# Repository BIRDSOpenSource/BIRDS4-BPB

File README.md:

<div align="center">
  
</div>

# BIRDS4-BPB
 Documentation for the Backplane Board used in the BIRDS4 Satellite

## About the BIRDS4 Program:

The Mission Statement of the Project is:

> “By successfully building and operating first satellite of nation, advance toward indigenous space program in each country”

The project is led by Kyushu Institute of Technology in Japan and involves students from Philippines, Paraguay, Nepal, Turkey and Japan.

Satellite Names: Tsuru (Japan), Guarani-1 (Paraguay) and Maya-2 (Phillipines)

Stakeholders:  Paraguayan Space Agency, Polytechnic Faculty of National University of Asuncion, and Kyushu Institute of Technology (Kyutech) for Japan.

Project duration: 2018-2022

CubeSat: 1U (10x10x10) cm3

Weight: 1.13kg

Launch Date: 21st February 2021 

BIRDS-4 has 1 main missions in total; APRS Store and forward mission

## Organisation structure

```bash

├── .gitattributes
├── B4_BPB_FM_PartsList_PBan_20191024.xls
├── BPB_v16.brd
├── BPB_v16.pdf
├── BPB_v16.sch
├── BPB_v16_BOT.png
├── BPB_v16_TOP.png
├── LICENSE
├── Photo.png
└── README.md

```

> [!CAUTION]
> The files `.sch` and `.brd` files in this repositiry were created using Eagle software.
 
For those that want to import these files into 
KiCAD7 [here's how you do it](https://community.element14.com/technologies/open-source-hardware/b/blog/posts/working-with-kicad-7-importing-eagle-files) 
 or KiCAD5.1 [here's how you do it](https://www.youtube.com/watch?v=RBc02MwpKxk&t=1s).
## Features

## I like this project, can I help you?
You are welcome 🙂

* Give us a star ⭐
* Watch repository to be notified about updates 👀
* If you will find some errors, report them in Issues 🐞
* Try Birds designs on some real computer and let us know how it worked in Discussions. 💬
* We would greatly appreciate if you would also tell others about this ecosystem, it helps us to improve BIRDS Open Source. Thank you!

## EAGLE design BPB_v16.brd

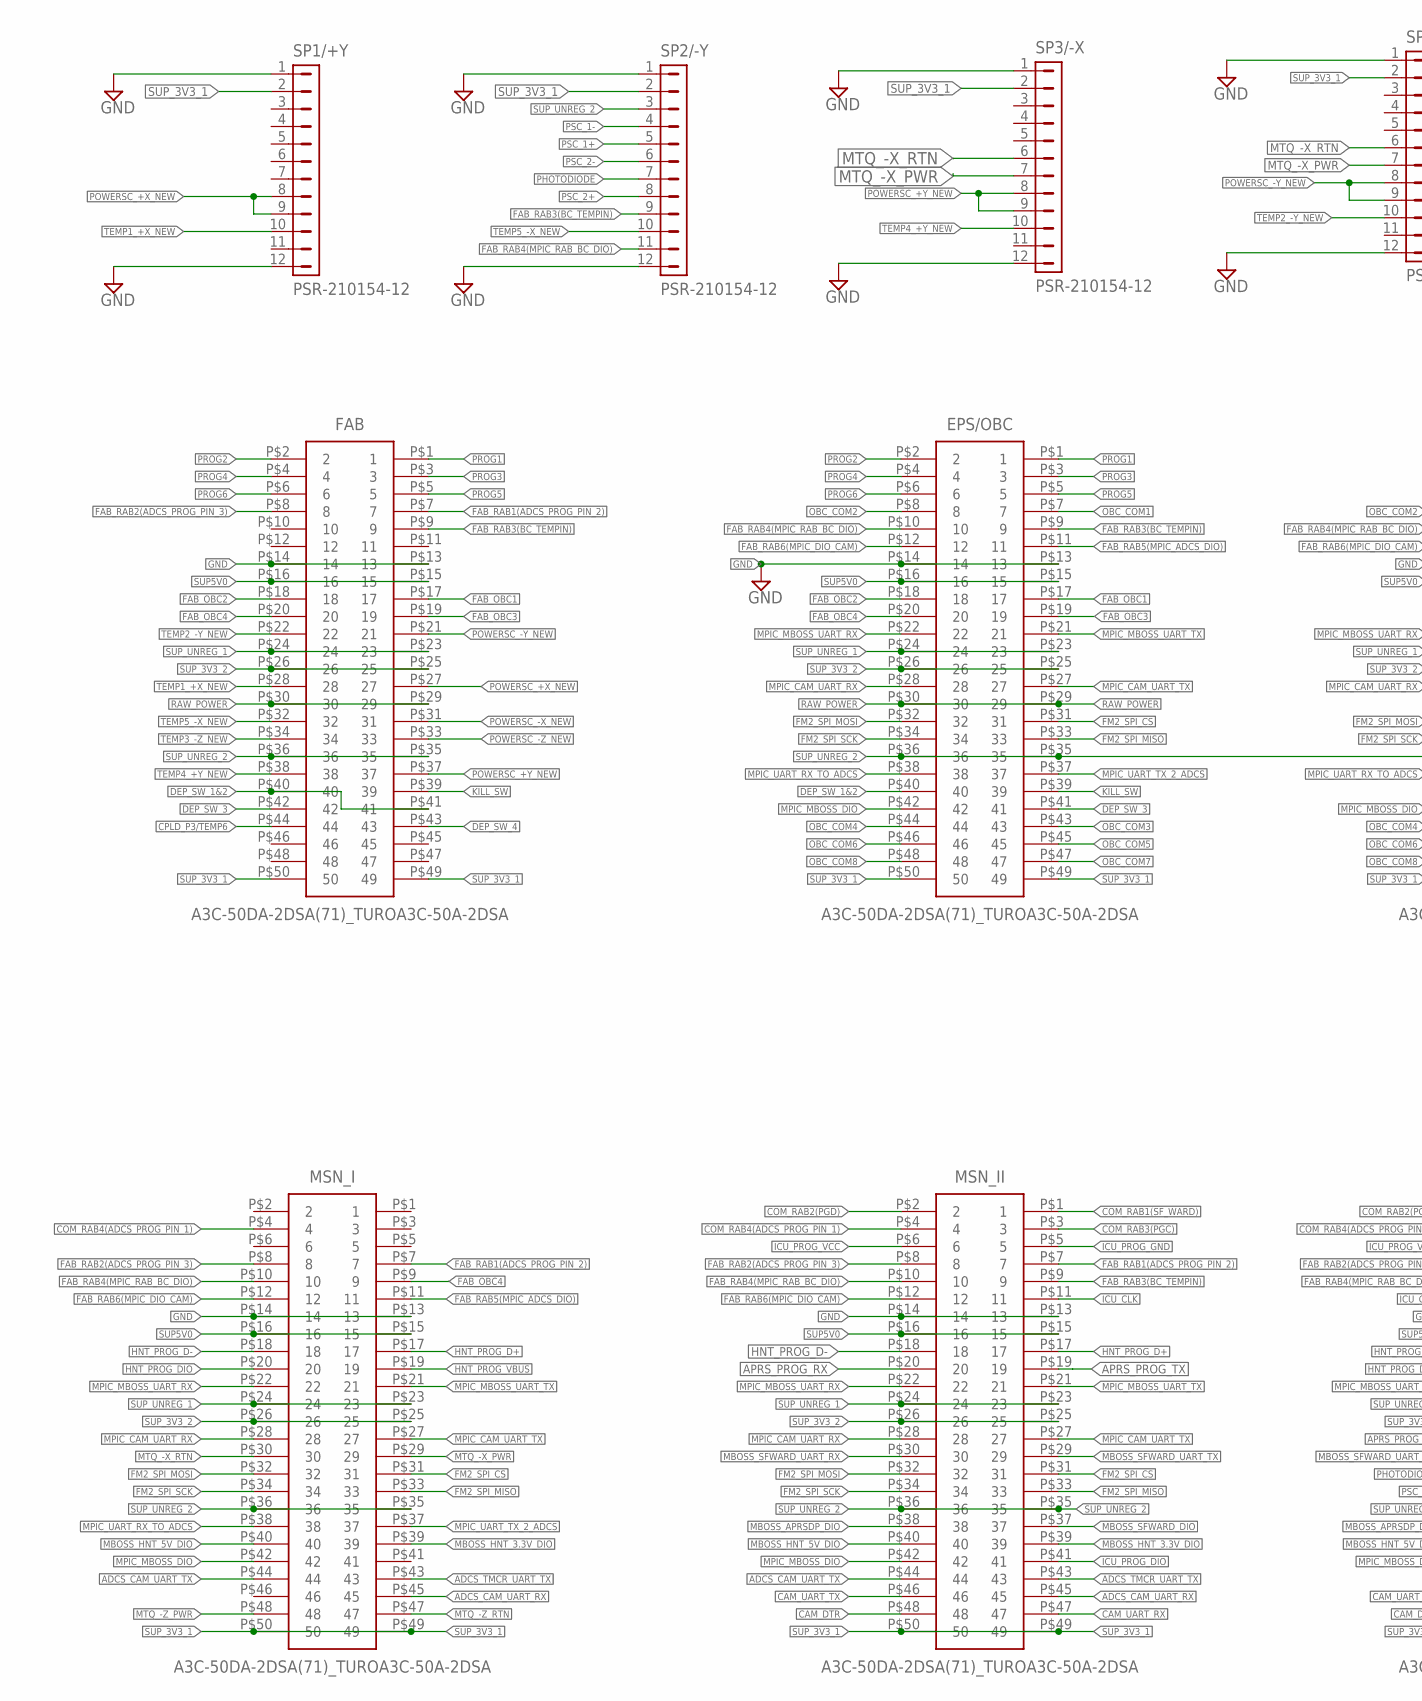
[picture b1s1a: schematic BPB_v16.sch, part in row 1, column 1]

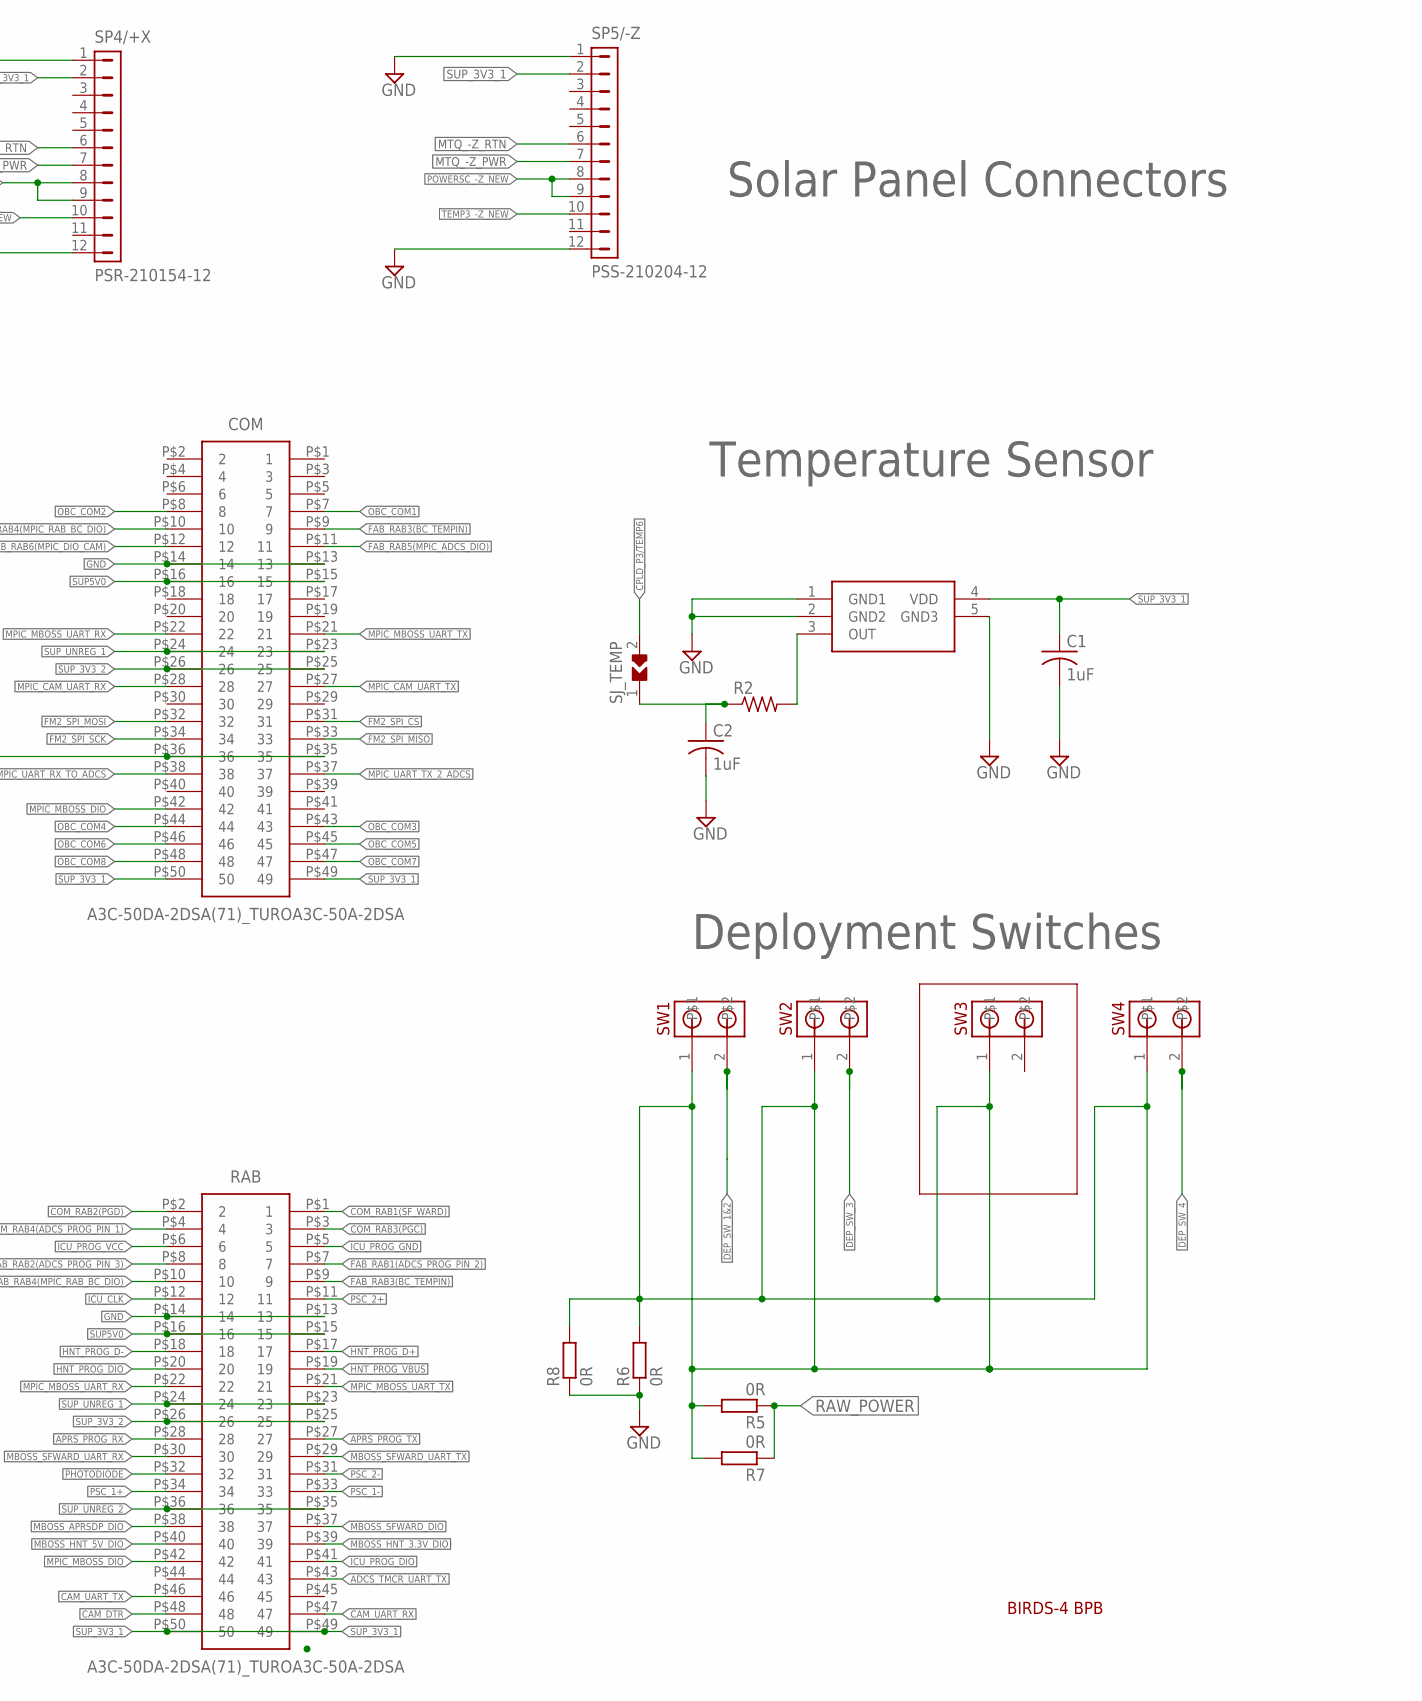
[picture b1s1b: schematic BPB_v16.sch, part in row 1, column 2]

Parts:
C1, C2: 1uF; C0603
COM: A3C-50DA-2DSA(71)_TUROA3C-50A-2DSA; SHDR50W60P200_2X25_5000X400X44_TR
EPS/OBC: A3C-50DA-2DSA(71)_TUROA3C-50A-2DSA; SHDR50W60P200_2X25_5000X400X44_TR
FAB: A3C-50DA-2DSA(71)_TUROA3C-50A-2DSA; SHDR50W60P200_2X25_5000X400X44_TR
MSN_I: A3C-50DA-2DSA(71)_TUROA3C-50A-2DSA; SHDR50W60P200_2X25_5000X400X44_TR
MSN_II: A3C-50DA-2DSA(71)_TUROA3C-50A-2DSA; SHDR50W60P200_2X25_5000X400X44_TR
R2: R-US_R0402; R0402
R5, R6, R7, R8: 0R; R3216
RAB: A3C-50DA-2DSA(71)_TUROA3C-50A-2DSA; SHDR50W60P200_2X25_5000X400X44_TR
SJ_TEMP: SJ_BY_TURO; SJ_TURO
SP1/+Y, SP2/-Y, SP3/-X, SP4/+X: PSR-210154-12; PIN1X12/90
SP5/-Z: PSS-210204-12; PIN1X12
SW1, SW2, SW3, SW4: MOLEX-CONN-2-0554600272; MOLEX-CONN-2-BIRDS
U$3: LMT84DCKT; SOT65P210X110-5N

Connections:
ADCS_CAM_UART_RX: MSN_I.P$45 (45), MSN_II.P$45 (45)
ADCS_CAM_UART_TX: MSN_I.P$44 (44), MSN_II.P$44 (44)
ADCS_TMCR_UART_TX: MSN_I.P$43 (43), MSN_II.P$43 (43), RAB.P$43 (43)
APRS_PROG_RX: MSN_II.P$20 (20), RAB.P$28 (28)
APRS_PROG_TX: MSN_II.P$19 (19), RAB.P$27 (27)
CAM_DTR: MSN_II.P$48 (48), RAB.P$48 (48)
CAM_UART_RX: MSN_II.P$47 (47), RAB.P$47 (47)
CAM_UART_TX: MSN_II.P$46 (46), RAB.P$46 (46)
COM_RAB1(SF_WARD): MSN_II.P$1 (1), RAB.P$1 (1)
COM_RAB2(PGD): MSN_II.P$2 (2), RAB.P$2 (2)
COM_RAB3(PGC): MSN_II.P$3 (3), RAB.P$3 (3)
COM_RAB4(ADCS_PROG_PIN_1): MSN_I.P$4 (4), MSN_II.P$4 (4), RAB.P$4 (4)
CPLD_P3/TEMP6: FAB.P$44 (44), SJ_TEMP.2
DEP_SW_1&2: EPS/OBC.P$40 (40), FAB.P$40 (40), FAB.P$41 (41), SW1.2
DEP_SW_3: EPS/OBC.P$41 (41), FAB.P$42 (42), SW2.2
DEP_SW_4: FAB.P$43 (43), SW4.2
DEP_SW_POWER: R5.2, R6.2, R7.2, R8.2, SW1.1, SW2.1, SW3.1, SW4.1
FAB_OBC1: EPS/OBC.P$17 (17), FAB.P$17 (17)
FAB_OBC2: EPS/OBC.P$18 (18), FAB.P$18 (18)
FAB_OBC3: EPS/OBC.P$19 (19), FAB.P$19 (19)
FAB_OBC4: EPS/OBC.P$20 (20), FAB.P$20 (20), MSN_I.P$9 (9)
FAB_RAB1(ADCS_PROG_PIN_2): FAB.P$7 (7), MSN_I.P$7 (7), MSN_II.P$7 (7), RAB.P$7 (7)
FAB_RAB2(ADCS_PROG_PIN_3): FAB.P$8 (8), MSN_I.P$8 (8), MSN_II.P$8 (8), RAB.P$8 (8)
FAB_RAB3(BC_TEMPIN): COM.P$9 (9), EPS/OBC.P$9 (9), FAB.P$9 (9), MSN_II.P$9 (9), RAB.P$9 (9), SP2/-Y.9
FAB_RAB4(MPIC_RAB_BC_DIO): COM.P$10 (10), EPS/OBC.P$10 (10), MSN_I.P$10 (10), MSN_II.P$10 (10), RAB.P$10 (10), SP2/-Y.11
FAB_RAB5(MPIC_ADCS_DIO): COM.P$11 (11), EPS/OBC.P$11 (11), MSN_I.P$11 (11)
FAB_RAB6(MPIC_DIO_CAM): COM.P$12 (12), EPS/OBC.P$12 (12), MSN_I.P$12 (12), MSN_II.P$12 (12)
FM2_SPI_CS: COM.P$31 (31), EPS/OBC.P$31 (31), MSN_I.P$31 (31), MSN_II.P$31 (31)
FM2_SPI_MISO: COM.P$33 (33), EPS/OBC.P$33 (33), MSN_I.P$33 (33), MSN_II.P$33 (33)
FM2_SPI_MOSI: COM.P$32 (32), EPS/OBC.P$32 (32), MSN_I.P$32 (32), MSN_II.P$32 (32)
FM2_SPI_SCK: COM.P$34 (34), EPS/OBC.P$34 (34), MSN_I.P$34 (34), MSN_II.P$34 (34)
GND: C1.2, C2.2, COM.P$13 (13), COM.P$14 (14), EPS/OBC.P$13 (13), EPS/OBC.P$14 (14), FAB.P$13 (13), FAB.P$14 (14), MSN_I.P$13 (13), MSN_I.P$14 (14), MSN_II.P$13 (13), MSN_II.P$14 (14), R6.1, R8.1, RAB.P$13 (13), RAB.P$14 (14), SP1/+Y.1, SP1/+Y.12, SP2/-Y.1, SP2/-Y.12, SP3/-X.1, SP3/-X.12, SP4/+X.1, SP4/+X.12, SP5/-Z.1, SP5/-Z.12, U$3.1 (GND1), U$3.2 (GND2), U$3.5 (GND3)
HNT_PROG_D+: MSN_I.P$17 (17), MSN_II.P$17 (17), RAB.P$17 (17)
HNT_PROG_D-: MSN_I.P$18 (18), MSN_II.P$18 (18), RAB.P$18 (18)
HNT_PROG_DIO: MSN_I.P$20 (20), RAB.P$20 (20)
HNT_PROG_VBUS: MSN_I.P$19 (19), RAB.P$19 (19)
ICU_CLK: MSN_II.P$11 (11), RAB.P$12 (12)
ICU_PROG_DIO: MSN_II.P$41 (41), RAB.P$41 (41)
ICU_PROG_GND: MSN_II.P$5 (5), RAB.P$5 (5)
ICU_PROG_VCC: MSN_II.P$6 (6), RAB.P$6 (6)
KILL_SW: EPS/OBC.P$39 (39), FAB.P$39 (39)
MBOSS_APRSDP_DIO: MSN_II.P$38 (38), RAB.P$38 (38)
MBOSS_HNT_3.3V_DIO: MSN_I.P$39 (39), MSN_II.P$39 (39), RAB.P$39 (39)
MBOSS_HNT_5V_DIO: MSN_I.P$40 (40), MSN_II.P$40 (40), RAB.P$40 (40)
MBOSS_SFWARD_DIO: MSN_II.P$37 (37), RAB.P$37 (37)
MBOSS_SFWARD_UART_RX: MSN_II.P$30 (30), RAB.P$30 (30)
MBOSS_SFWARD_UART_TX: MSN_II.P$29 (29), RAB.P$29 (29)
MPIC_CAM_UART_RX: COM.P$28 (28), EPS/OBC.P$28 (28), MSN_I.P$28 (28), MSN_II.P$28 (28)
MPIC_CAM_UART_TX: COM.P$27 (27), EPS/OBC.P$27 (27), MSN_I.P$27 (27), MSN_II.P$27 (27)
MPIC_MBOSS_DIO: COM.P$42 (42), EPS/OBC.P$42 (42), MSN_I.P$42 (42), MSN_II.P$42 (42), RAB.P$42 (42)
MPIC_MBOSS_UART_RX: COM.P$22 (22), EPS/OBC.P$22 (22), MSN_I.P$22 (22), MSN_II.P$22 (22), RAB.P$22 (22)
MPIC_MBOSS_UART_TX: COM.P$21 (21), EPS/OBC.P$21 (21), MSN_I.P$21 (21), MSN_II.P$21 (21), RAB.P$21 (21)
MPIC_UART_RX_TO_ADCS: COM.P$38 (38), EPS/OBC.P$38 (38), MSN_I.P$38 (38)
MPIC_UART_TX_2_ADCS: COM.P$37 (37), EPS/OBC.P$37 (37), MSN_I.P$37 (37)
MTQ_-X_PWR: MSN_I.P$29 (29), SP3/-X.7, SP4/+X.7
MTQ_-X_RTN: MSN_I.P$30 (30), SP3/-X.6, SP4/+X.6
MTQ_-Z_PWR: MSN_I.P$48 (48), SP5/-Z.7
MTQ_-Z_RTN: MSN_I.P$47 (47), SP5/-Z.6
unnamed: C2.1, R2.1, SJ_TEMP.1
unnamed: R2.2, U$3.3 (OUT)
OBC_COM1: COM.P$7 (7), EPS/OBC.P$7 (7)
OBC_COM2: COM.P$8 (8), EPS/OBC.P$8 (8)
OBC_COM3: COM.P$43 (43), EPS/OBC.P$43 (43)
OBC_COM4: COM.P$44 (44), EPS/OBC.P$44 (44)
OBC_COM5: COM.P$45 (45), EPS/OBC.P$45 (45)
OBC_COM6: COM.P$46 (46), EPS/OBC.P$46 (46)
OBC_COM7: COM.P$47 (47), EPS/OBC.P$47 (47)
OBC_COM8: COM.P$48 (48), EPS/OBC.P$48 (48)
PHOTODIODE: RAB.P$32 (32), SP2/-Y.7
POWERSC_+X_NEW: FAB.P$27 (27), SP1/+Y.8, SP1/+Y.9
POWERSC_+Y_NEW: FAB.P$37 (37), SP3/-X.8, SP3/-X.9
POWERSC_-X_NEW: FAB.P$31 (31)
POWERSC_-Y_NEW: FAB.P$21 (21), SP4/+X.8, SP4/+X.9
POWERSC_-Z_NEW: FAB.P$33 (33), SP5/-Z.8, SP5/-Z.9
PROG1: EPS/OBC.P$1 (1), FAB.P$1 (1)
PROG2: EPS/OBC.P$2 (2), FAB.P$2 (2)
PROG3: EPS/OBC.P$3 (3), FAB.P$3 (3)
PROG4: EPS/OBC.P$4 (4), FAB.P$4 (4)
PROG5: EPS/OBC.P$5 (5), FAB.P$5 (5)
PROG6: EPS/OBC.P$6 (6), FAB.P$6 (6)
PSC_1+: RAB.P$34 (34), SP2/-Y.5
PSC_1-: RAB.P$33 (33), SP2/-Y.4
PSC_2+: RAB.P$11 (11), SP2/-Y.8
PSC_2-: RAB.P$31 (31), SP2/-Y.6
RAW_POWER: EPS/OBC.P$29 (29), EPS/OBC.P$30 (30), FAB.P$29 (29), FAB.P$30 (30), R5.1, R7.1
SUP5V0: COM.P$15 (15), COM.P$16 (16), EPS/OBC.P$15 (15), EPS/OBC.P$16 (16), FAB.P$15 (15), FAB.P$16 (16), MSN_I.P$15 (15), MSN_I.P$16 (16), MSN_II.P$15 (15), MSN_II.P$16 (16), RAB.P$15 (15), RAB.P$16 (16)
SUP_3V3_1: C1.1, COM.P$49 (49), COM.P$50 (50), EPS/OBC.P$49 (49), EPS/OBC.P$50 (50), FAB.P$49 (49), FAB.P$50 (50), MSN_I.P$49 (49), MSN_I.P$50 (50), MSN_II.P$49 (49), MSN_II.P$50 (50), RAB.P$49 (49), RAB.P$50 (50), SP1/+Y.2, SP2/-Y.2, SP3/-X.2, SP4/+X.2, SP5/-Z.2, U$3.4 (VDD)
SUP_3V3_2: COM.P$25 (25), COM.P$26 (26), EPS/OBC.P$25 (25), EPS/OBC.P$26 (26), FAB.P$25 (25), FAB.P$26 (26), MSN_I.P$25 (25), MSN_I.P$26 (26), MSN_II.P$25 (25), MSN_II.P$26 (26), RAB.P$25 (25), RAB.P$26 (26)
SUP_UNREG_1: COM.P$23 (23), COM.P$24 (24), EPS/OBC.P$23 (23), EPS/OBC.P$24 (24), FAB.P$23 (23), FAB.P$24 (24), MSN_I.P$23 (23), MSN_I.P$24 (24), MSN_II.P$23 (23), MSN_II.P$24 (24), RAB.P$23 (23), RAB.P$24 (24)
SUP_UNREG_2: COM.P$35 (35), COM.P$36 (36), EPS/OBC.P$35 (35), EPS/OBC.P$36 (36), FAB.P$35 (35), FAB.P$36 (36), MSN_I.P$35 (35), MSN_I.P$36 (36), MSN_II.P$35 (35), MSN_II.P$36 (36), RAB.P$35 (35), RAB.P$36 (36), SP2/-Y.3
TEMP1_+X_NEW: FAB.P$28 (28), SP1/+Y.10
TEMP2_-Y_NEW: FAB.P$22 (22), SP4/+X.10
TEMP3_-Z_NEW: FAB.P$34 (34), SP5/-Z.10
TEMP4_+Y_NEW: FAB.P$38 (38), SP3/-X.10
TEMP5_-X_NEW: FAB.P$32 (32), SP2/-Y.10

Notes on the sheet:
Temperature Sensor
Deployment Switches
Solar Panel Connectors
BIRDS-4 BPB

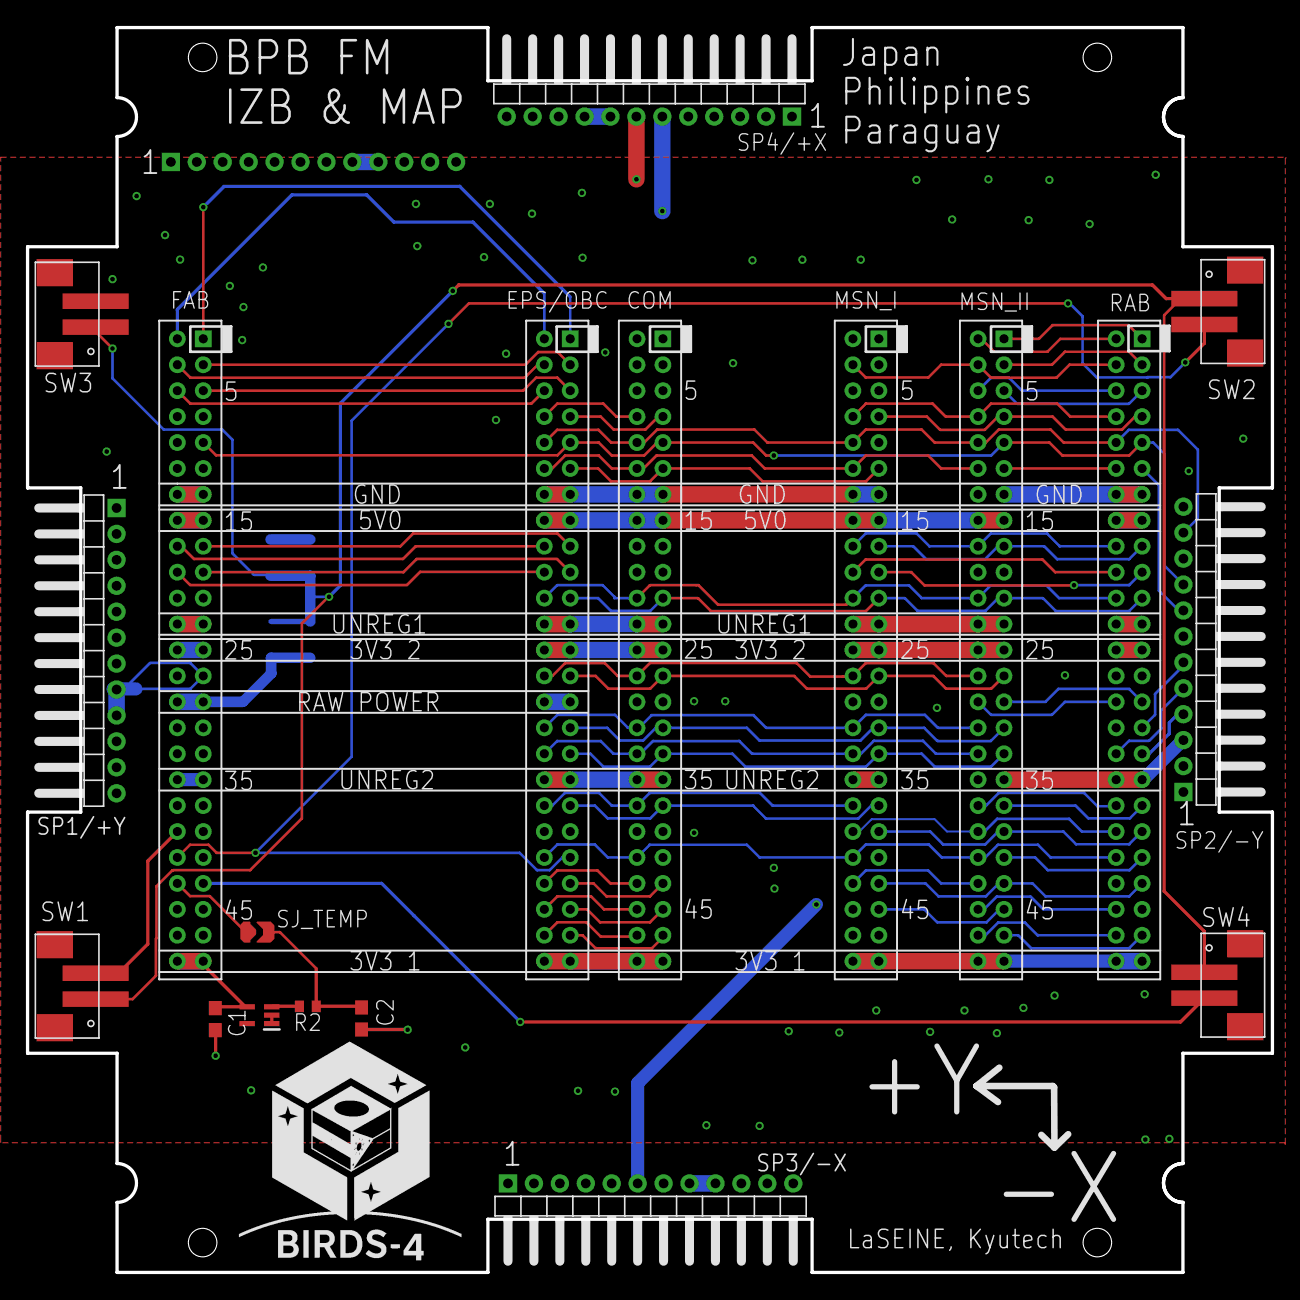
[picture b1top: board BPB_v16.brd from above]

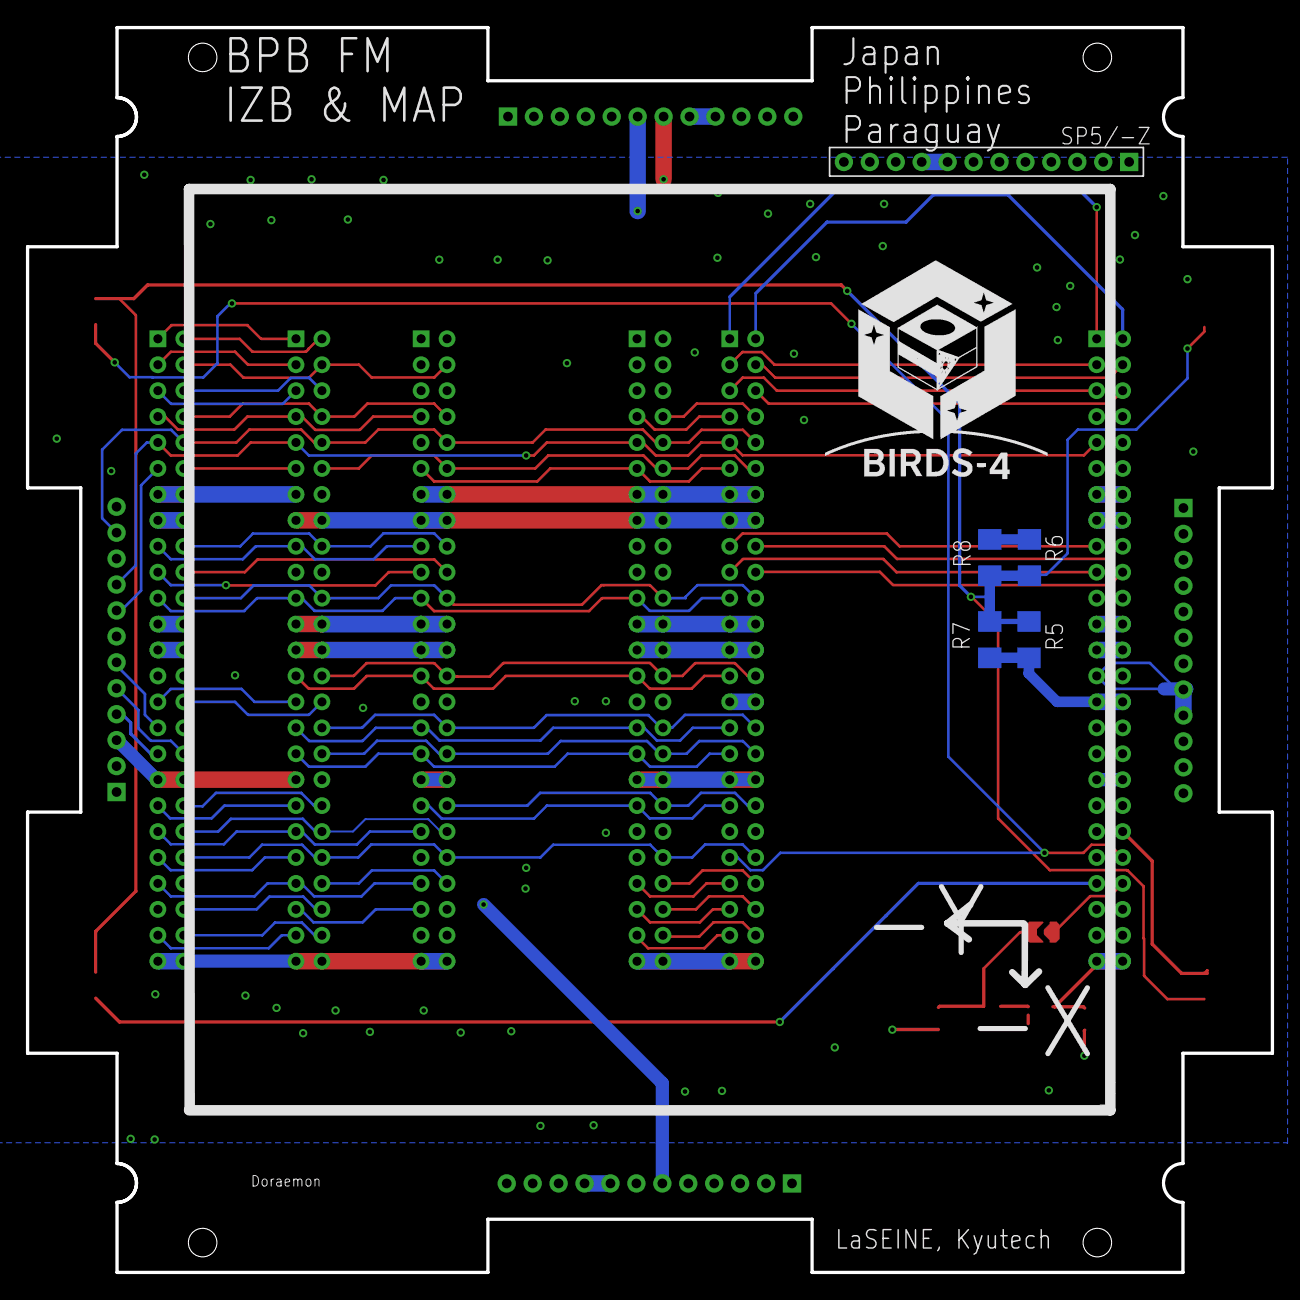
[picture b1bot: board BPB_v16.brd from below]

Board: 4 copper layers, 96.0 x 96.0 mm, 24 parts (5 on the bottom side), 94 nets.
